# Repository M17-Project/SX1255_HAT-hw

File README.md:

[![CC BY-NC-SA 4.0][cc-by-nc-sa-shield]][cc-by-nc-sa]

# SX1255_HAT-hw
Raspberry Pi Zero shield with the SX1255 RF transceiver chip.

Revision B. Work in progress. Do not order.

## Revision B

Revision B is for series production. Changes from revision A:

- All parts come from the shared [M17 KiCad library](https://github.com/M17-Project/M17_kicad_library)
  (git submodule `lib/`). Each part has its manufacturer, MPN, Mouser and LCSC numbers.
- 4 layer board, JLCPCB stackup `JLC04101H-7628` (1.0 mm). The RF lines are 50 Ω
  grounded coplanar waveguides on the top layer over a ground plane.
- Passive parts are 0402. The RF inductors and capacitors are Murata high Q parts.
- ID EEPROM (AT24C32D, address 0x50) for the Raspberry Pi HAT format.
  The ID_SD and ID_SC pull-ups are 3.9 kΩ and the WP pull-up is 1 kΩ, as the
  Raspberry Pi HAT design guide specifies. Connect test point TP4 (WP) to TP5 (GND) to write the EEPROM.
- The RF supply (+3V3_RF) comes from a low noise LDO (LP5907MFX-3.3) on the 5 V pins of the GPIO header.
  NCP163ASN330T1G and TPS7A2033PDBVR are drop-in alternates.
- A 100 pF capacitor connects the TCXO output to the SX1255 XTB pin, as in the Semtech reference design.
- Low cost Adam Tech RF2-04A-T-00-50-G SMA connectors, as in revision A.

The GPIO header pinout is the same as in revision A.

| Signal | GPIO header pin | Raspberry Pi function |
|---|---|---|
| SX1255 SCK, MOSI, MISO | 23, 19, 21 | SPI0 |
| SX1255 NSS | 24 | SPI0 CE0 (GPIO8) |
| SX1255 RESET | 22 | GPIO25 |
| SX1255 CK_OUT | 12 | PCM CLK (GPIO18) |
| SX1255 DIO2 | 35 | PCM FS (GPIO19) |
| SX1255 I_OUT | 38 | PCM DIN (GPIO20) |
| SX1255 I_IN | 40 | PCM DOUT (GPIO21) |
| ID EEPROM | 27, 28 | ID_SD, ID_SC |

> [!NOTE]
> In case the TCXO used in the project is not available, `TG2016SMN 32.0000M-MCGNNM0` is a valid replacement (0.5ppm frequency stability).
> Alternatively, `ECS-TXO-20CSMV-320-EY` can be used (2.5ppm frequency stability).

## Basic specifications
| Parameter                       | Value                                       |
|---------------------------------|---------------------------------------------|
| Tuning range                    | 400 to 510MHz (356 to 562MHz out-of-spec)   |
| RF output power                 | +5dBm typ. (1dB compression point)          |
| Baseband interface              | I2S (master)                                |
| Frequency synthesizer step size | ~30.5Hz                                     |
| RX gain range                   | 70dB                                        |

See the [SX1255 datasheet](https://www.semtech.com/products/wireless-rf/lora-core/sx1255) for more details.

## Get the files

Clone the repository with the library submodule:

```sh
git clone --recursive https://github.com/M17-Project/SX1255_HAT-hw.git
```

If you cloned without `--recursive`, get the library:

```sh
git submodule update --init
```

## Build

Install KiCad 10 and KiKit. Then run:

```sh
make
```

The build checks the design first. Any ERC or DRC violation stops the build.
Each part on the BOM must have a Mouser number. The outputs are in `build/`.
If a part is not in stock, use a drop-in alternate from `build/bom/SX1255_HAT-hw_bom_alternates.csv`.

To use the same tools as the CI, run the build in Docker:

```sh
make docker
```

To update the library, run `make lib-update`.

## Usage
### RPi sample config code
Sample Raspberry Pi code for SX1255 control can be found [here](https://github.com/M17-Project/LinHT-utils/tree/main/sx1255).<br>
[I2S slave overlay](https://github.com/AkiyukiOkayasu/RaspberryPi_I2S_Slave) is required. Sample rate for both RX and TX can be set to 125, 250, or 500kHz.

RX/TX frequency setting (500kHz sample rate):
```
./sx1255-spi -s 500 -r 435000000 -t 438000000
```

### Example RX with ZeroMQ
```
arecord -t raw -f S32_LE -r 192000 -c 2 --device="hw:0,1" | ./int_to_short | ./zmq-pub
```

In which `int_to_short` is a simple `int` to `short` format converter:
```C
while(1)
{
  ioctl(STDIN_FILENO, FIONREAD, &rcvd);
  if(rcvd>0)
  {
    if(read(STDIN_FILENO, inp, rcvd)==rcvd)
    {
      for(int i=0; i<rcvd; i+=8)
      {
        memcpy(&out[i/2  ], &inp[i  +2], 2);
        memcpy(&out[i/2+2], &inp[i+4+2], 2);
      }

      write(STDOUT_FILENO, out, rcvd/2);
    }
  }
}
```

### Example TX with ZeroMQ
```
./zmq-sub 192.168.50.243:17018 | aplay -t raw -f S32_LE -r 192000 -c 2 --device="hw:0,0"
```

## Example GNU Radio flowgraphs
There are 2 demo flowgraphs available:
- [*cari_sx1255_rx_demo.grc*](https://github.com/M17-Project/CARI/blob/main/gr_demos/cari_sx1255_rx_demo.grc)
- [*cari_sx1255_multicarrier_tx_demo.grc*](https://github.com/M17-Project/CARI/blob/main/gr_demos/cari_sx1255_multicarrier_tx_demo.grc)

The RX demo also provides a set of sinc compensating FIR filter taps through the `Decimating FIR Filter` block.

## License
This work is licensed under a
[Creative Commons Attribution-NonCommercial-ShareAlike 4.0 International License][cc-by-nc-sa].

[![CC BY-NC-SA 4.0][cc-by-nc-sa-image]][cc-by-nc-sa]

[cc-by-nc-sa]: http://creativecommons.org/licenses/by-nc-sa/4.0/
[cc-by-nc-sa-image]: https://licensebuttons.net/l/by-nc-sa/4.0/88x31.png
[cc-by-nc-sa-shield]: https://img.shields.io/badge/License-CC%20BY--NC--SA%204.0-lightgrey.svg

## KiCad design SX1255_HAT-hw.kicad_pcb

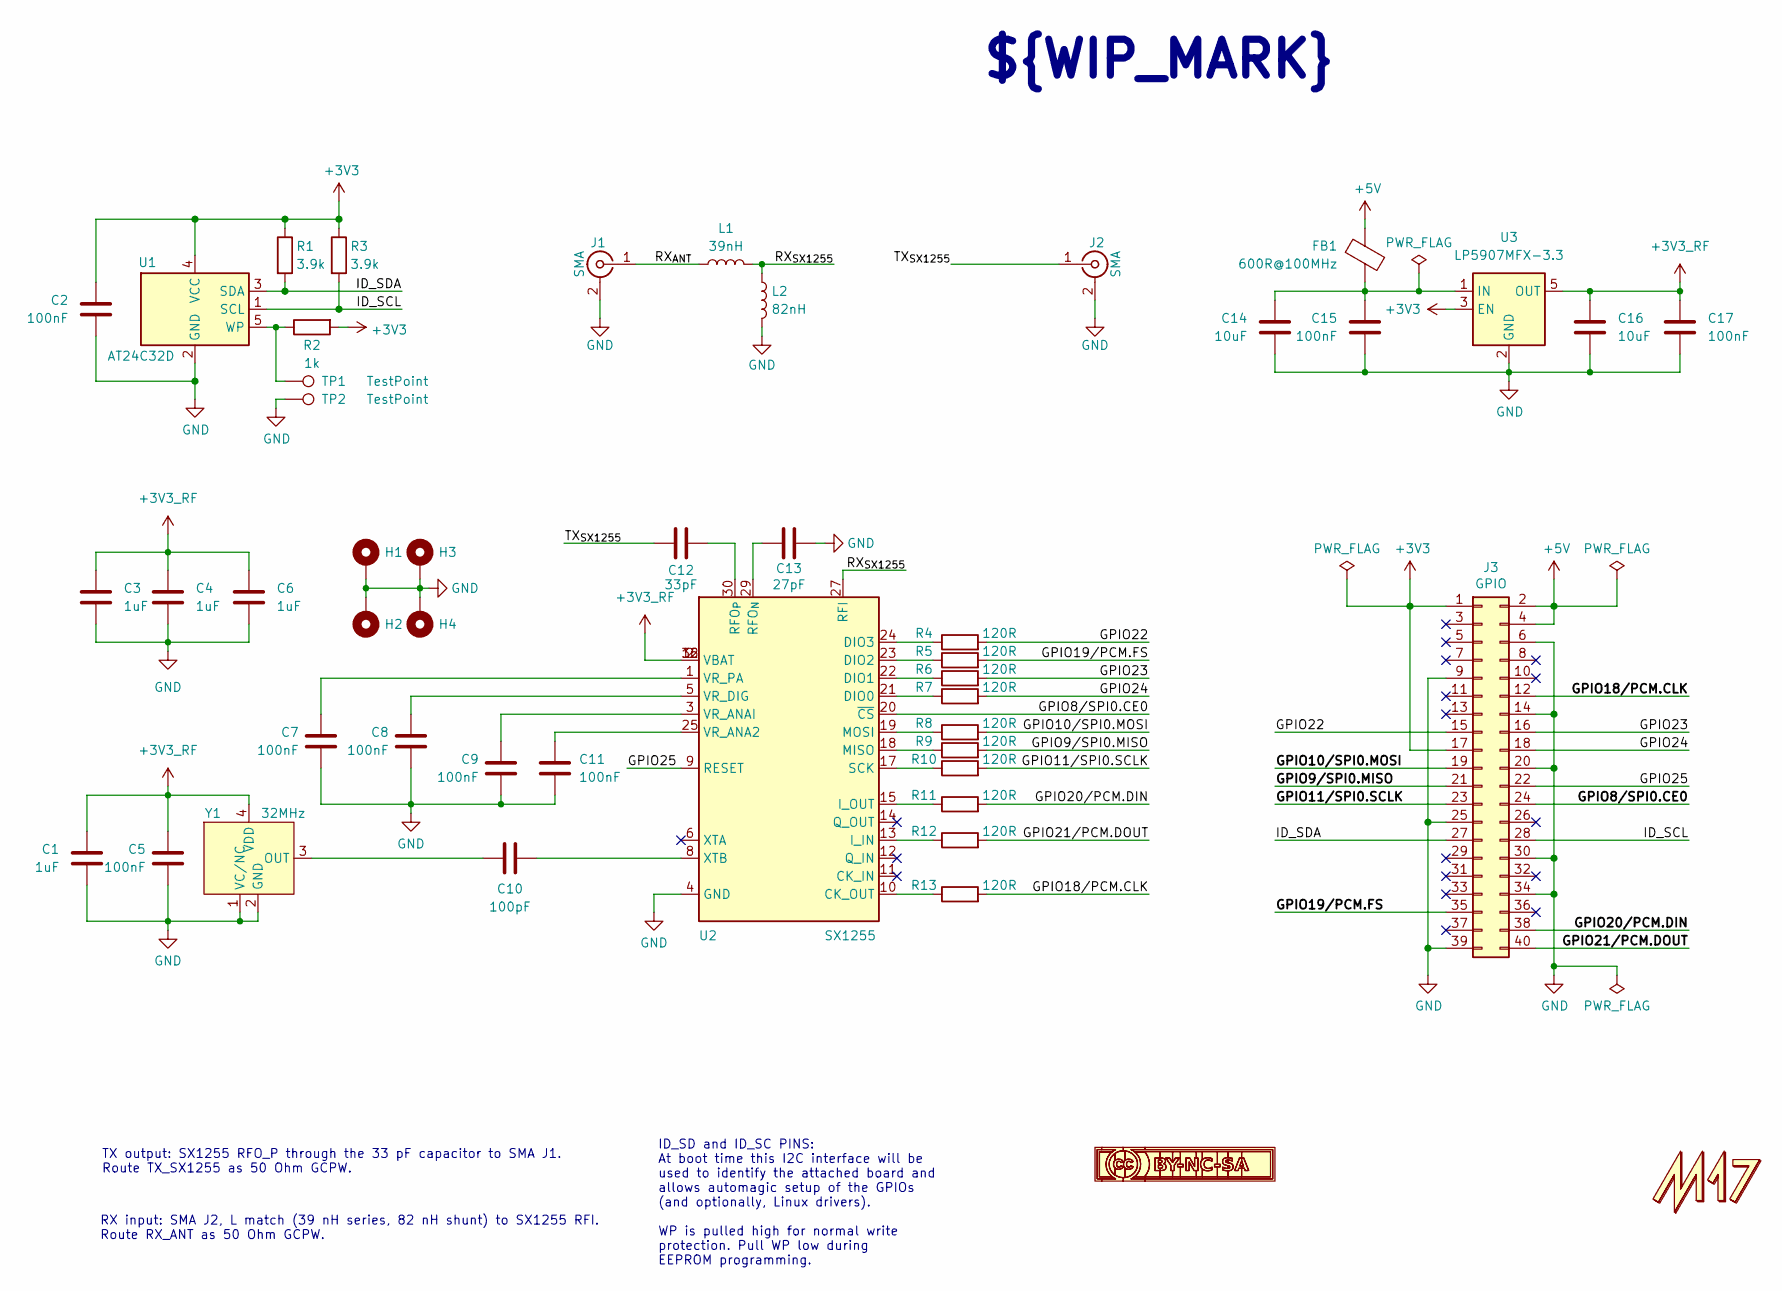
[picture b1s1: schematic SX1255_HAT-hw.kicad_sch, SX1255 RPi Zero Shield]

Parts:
C1, C3, C4, C6: 1uF; C_0402_1005Metric; Tolerance ±10%; Voltage 25V; MPN CL05A105KA5NQNC; Mouser 187-CL05A105KA5NQNC
C2, C5, C7, C8, C9, C11, C15, C17: 100nF; C_0402_1005Metric; Tolerance ±10%; Voltage 50V; MPN CL05B104KB54PNC; Mouser 187-CL05B104KB54PNC
C10: 100pF; C_0402_1005Metric; Tolerance ±5%; Voltage 50V; MPN GRM1555C1H101JA01D; Mouser 81-GRM1555C1H101JA1D
C12: 33pF; C_0402_1005Metric; Tolerance ±1%; Voltage 50V; MPN GJM1555C1H330FB01D; Mouser 81-GJM1555C1H330FB1D
C13: 27pF; C_0402_1005Metric; Tolerance ±1%; Voltage 50V; MPN GJM1555C1H270FB01D; Mouser 81-GJM1555C1H270FB1D
C14, C16: 10uF; C_0805_2012Metric; Tolerance ±10%; Voltage 25V; MPN CL21A106KAYNNNE; Mouser 187-CL21A106KAYNNNE
FB1: 600R@100MHz; L_0402_1005Metric; Tolerance ±25%; MPN BLM15PX601SN1D; Mouser 81-BLM15PX601SN1D
H1, H2, H3, H4: MountingHole; MountingHole_2.7mm_M2.5_Pad_Via
J1, J2: SMA; SMA_AdamTech_RF2-04A-T-00-50-G_Vertical; MPN RF2-04A-T-00-50-G; Mouser 737-RF204AT0050G
J3: GPIO; PinSocket_2x20_P2.54mm_Vertical; MPN M20-7832046; Mouser 855-M20-7832046
L1: 39nH; L_0402_1005Metric; Tolerance ±2%; MPN LQW15AN39NG00D; Mouser 81-LQW15AN39NG00D
L2: 82nH; L_0402_1005Metric; Tolerance ±2%; MPN LQW15AN82NG00D; Mouser 81-LQW15AN82NG00D
LOGO1: CC BY-NC-SA 4.0; Logo_CC_BY-NC-SA_4.0_17mm_SilkScreen
LOGO2: M17; Logo_M17_12mm_SilkScreen
R1, R3: 3.9k; R_0402_1005Metric; Tolerance ±1%; Voltage 50V; MPN 0402WGF3901TCE; Mouser 303-0402WGF3901TCE
R2: 1k; R_0402_1005Metric; Tolerance ±1%; Voltage 50V; MPN 0402WGF1001TCE; Mouser 303-0402WGF1001TCE
R4, R5, R6, R7, R8, R9, R10, R11, R12, R13: 120R; R_0402_1005Metric; Tolerance ±1%; Voltage 50V; MPN 0402WGF1200TCE; Mouser 303-0402WGF1200TCE
TP1, TP2: TestPoint; TestPoint_Pad_D1.0mm
U1: AT24C32D; SOT-23-5; MPN AT24C32D-STUM-T; Mouser 556-AT24C32D-STUM-T
U2: SX1255; QFN-32-1EP_5x5mm_P0.5mm_EP3.3x3.3mm_ThermalVias; Mouser Part Number 947-SX1255IWLTRT
U3: LP5907MFX-3.3; SOT-23-5; MPN LP5907MFX-3.3/NOPB; Mouser 595-LP5907MFX-3.3NPB
Y1: 32MHz; ECS-TXO-20CSMV4_2.0x1.6mm; MPN TG2016SMN 32.0000M-MCGNNM3; Mouser 732-216SMN32MMCGNNM3

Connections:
+3V3: C2.1, J3.1, J3.17, R1.1, R2.2, R3.1, U1.4 (VCC), U3.3 (EN)
+3V3_RF: C1.1, C3.1, C4.1, C5.1, C6.1, C16.1, C17.1, U2.2 (VBAT), U2.16 (VBAT), U2.32 (VBAT), U3.5 (OUT), Y1.4 (VDD)
+5V: FB1.1, J3.2, J3.4
/GPIO8/SPI0.CE0: J3.24, U2.20 (~CS)
/GPIO9/SPI0.MISO: J3.21, R9.2
/GPIO10/SPI0.MOSI: J3.19, R8.2
/GPIO11/SPI0.SCLK: J3.23, R10.2
/GPIO18/PCM.CLK: J3.12, R13.2
/GPIO19/PCM.FS: J3.35, R5.2
/GPIO20/PCM.DIN: J3.38, R11.2
/GPIO21/PCM.DOUT: J3.40, R12.2
/GPIO22: J3.15, R4.2
/GPIO23: J3.16, R6.2
/GPIO24: J3.18, R7.2
/GPIO25: J3.22, U2.9 (RESET)
/ID_SCL: J3.28, R3.2, U1.1 (SCL)
/ID_SDA: J3.27, R1.2, U1.3 (SDA)
/RX_{ANT}: J1.1 (In), L1.1
/RX_{SX1255}: L1.2, L2.1, U2.27 (RFI)
/TX_{SX1255}: C12.1, J2.1 (In)
GND: C1.2, C2.2, C3.2, C4.2, C5.2, C6.2, C7.2, C8.2, C9.2, C11.2, C13.2, C14.2, C15.2, C16.2, C17.2, H1.1 (1_1), H2.1 (1_1), H3.1 (1_1), H4.1 (1_1), J1.2 (Ext), J2.2 (Ext), J3.6, J3.9, J3.14, J3.20, J3.25, J3.30, J3.34, J3.39, L2.2, TP2.1 (1_1), U1.2 (GND), U2.4 (GND), U2.7 (GND), U2.26 (GND), U2.28 (GND), U2.31 (GND), U2.33 (GND), U3.2 (GND), Y1.1 (VC/NC), Y1.2 (GND)
unnamed: R2.1, TP1.1 (1_1), U1.5 (WP)
unnamed: R13.1, U2.10 (CK_OUT)
unnamed: R7.1, U2.21 (DIO0)
unnamed: R6.1, U2.22 (DIO1)
unnamed: R5.1, U2.23 (DIO2)
unnamed: R4.1, U2.24 (DIO3)
unnamed: R12.1, U2.13 (I_IN)
unnamed: R11.1, U2.15 (I_OUT)
unnamed: R9.1, U2.18 (MISO)
unnamed: R8.1, U2.19 (MOSI)
unnamed: C13.1, U2.29 (RFO_{N})
unnamed: C12.2, U2.30 (RFO_{P})
unnamed: R10.1, U2.17 (SCK)
unnamed: C11.1, U2.25 (VR_ANA2)
unnamed: C9.1, U2.3 (VR_ANAI)
unnamed: C8.1, U2.5 (VR_DIG)
unnamed: C7.1, U2.1 (VR_PA)
unnamed: C10.1, U2.8 (XTB)
unnamed: C14.1, C15.1, FB1.2, U3.1 (IN)
unnamed: C10.2, Y1.3 (OUT)

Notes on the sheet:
${WIP_MARK}
ID_SD and ID_SC PINS: At boot time this I2C interface will be used to identify the attached board and allows automagic setup of the GPIOs (and optionally, Linux drivers). WP is pulled high for normal write protection. Pull WP low during EEPROM programming.
TX output: SX1255 RFO_P through the 33 pF capacitor to SMA J1. Route TX_SX1255 as 50 Ohm GCPW.
RX input: SMA J2, L match (39 nH series, 82 nH shunt) to SX1255 RFI. Route RX_ANT as 50 Ohm GCPW.

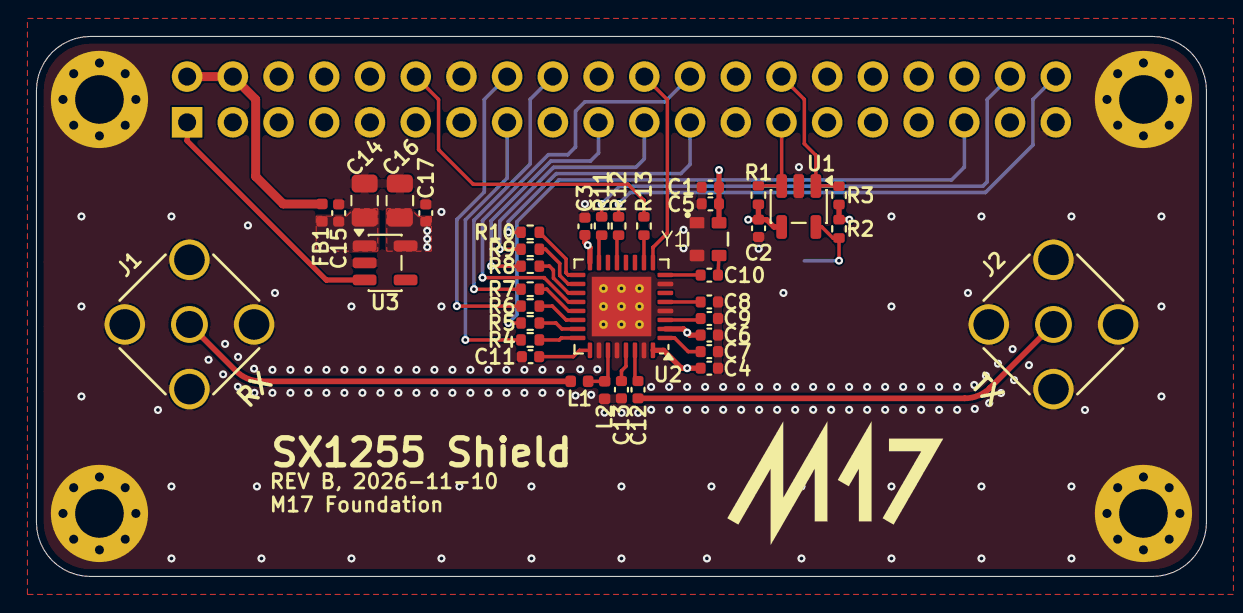
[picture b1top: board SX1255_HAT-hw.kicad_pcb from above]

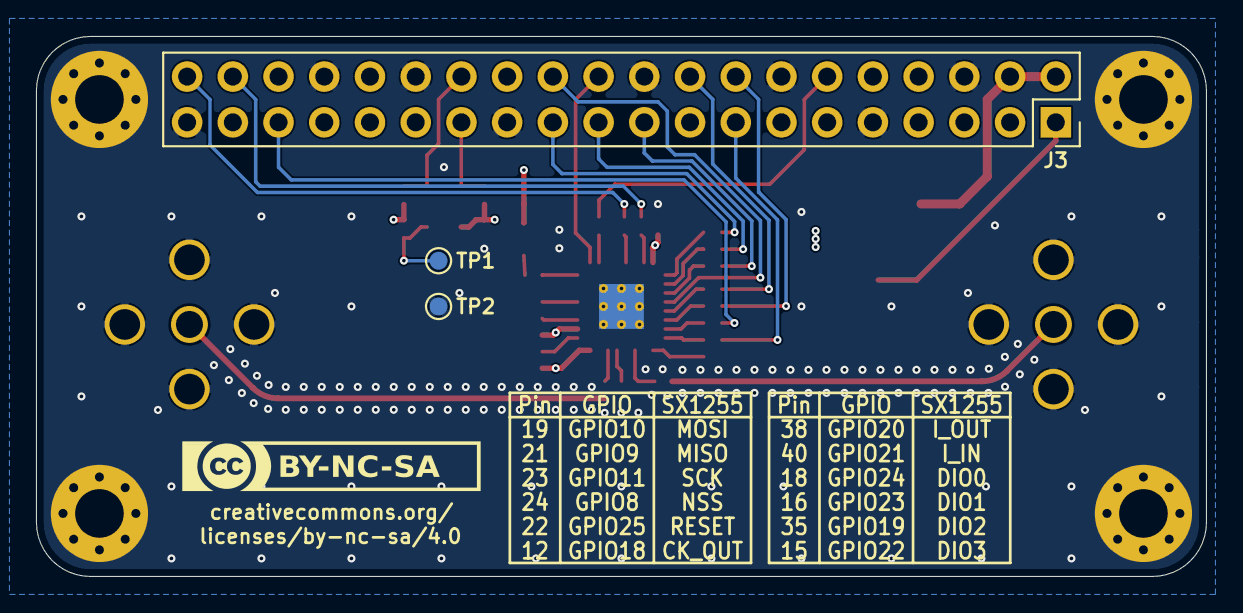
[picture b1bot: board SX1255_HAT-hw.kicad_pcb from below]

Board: 4 copper layers, 65.0 x 30.0 mm, 48 parts (4 on the bottom side), 41 nets.

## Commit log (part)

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2025-02-07 init
2025-02-08 pcb update
2025-02-08 BOM and silkscreen updates
2025-02-08 readme update
2025-02-08 re-routed one of the tracks
2025-02-10 MPN fixes for Mouser
2025-06-04 SX1255 library update
2025-11-11 Revise usage instructions for SX1255 control
    Updated Raspberry Pi code link and sample rate details.
2025-11-11 Fix command syntax in README for sx1255-spi
2025-12-04 Update README with TCXO replacement information
    Added note about TCXO replacement for the project.
2026-03-10 Update TCXO replacement options in README
    Added alternative TCXO replacement with frequency stability details.

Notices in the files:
parts and their libraries:
Creative Commons BY-NC-SA 4.0 license button (official 80x15 button) with the deed URI https://creativecommons.org/licenses/by-nc-sa/4.0
https://creativecommons.org/licenses/by-nc-sa/4.0
Creative Commons BY-NC-SA 4.0 license button and deed URI on the silkscreen. Use it on boards under this license
